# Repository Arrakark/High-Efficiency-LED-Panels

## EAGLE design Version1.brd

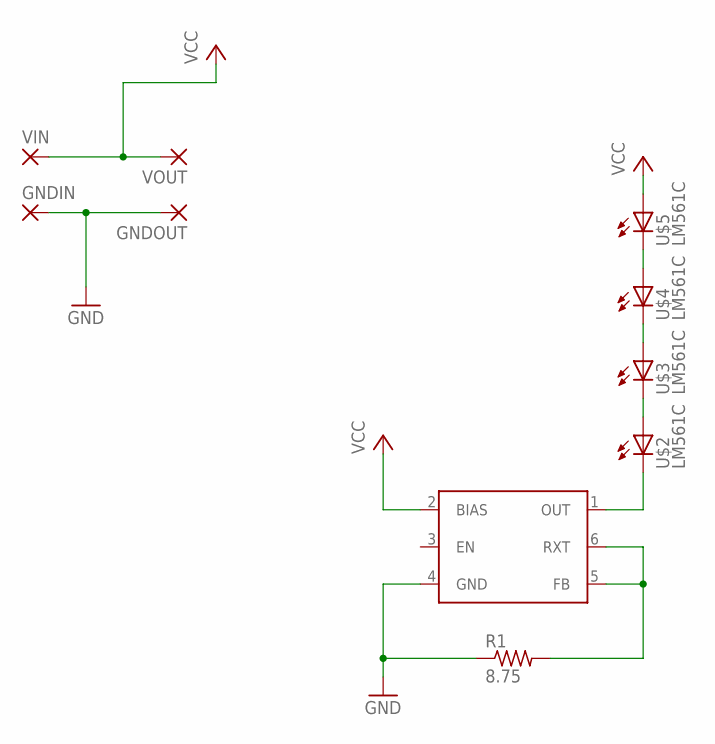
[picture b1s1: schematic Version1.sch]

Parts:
GNDIN: SMD5; SMD2,54-5,08
GNDOUT: SMD5; SMD2,54-5,08
R1: 8.75; R0805
U$1: AL5802; SOT26
U$2, U$3, U$4, U$5: LM561C; LM561CPAD
VIN: SMD5; SMD2,54-5,08
VOUT: SMD5; SMD2,54-5,08

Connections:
GND: GNDIN.1, GNDOUT.1, R1.1, U$1.4 (GND)
unnamed: R1.2, U$1.5 (FB), U$1.6 (RXT)
unnamed: U$4.ANODE (A), U$5.CATH (C)
unnamed: U$3.ANODE (A), U$4.CATH (C)
unnamed: U$2.ANODE (A), U$3.CATH (C)
unnamed: U$1.1 (OUT), U$2.CATH (C)
VCC: U$1.2 (BIAS), U$5.ANODE (A), VIN.1, VOUT.1

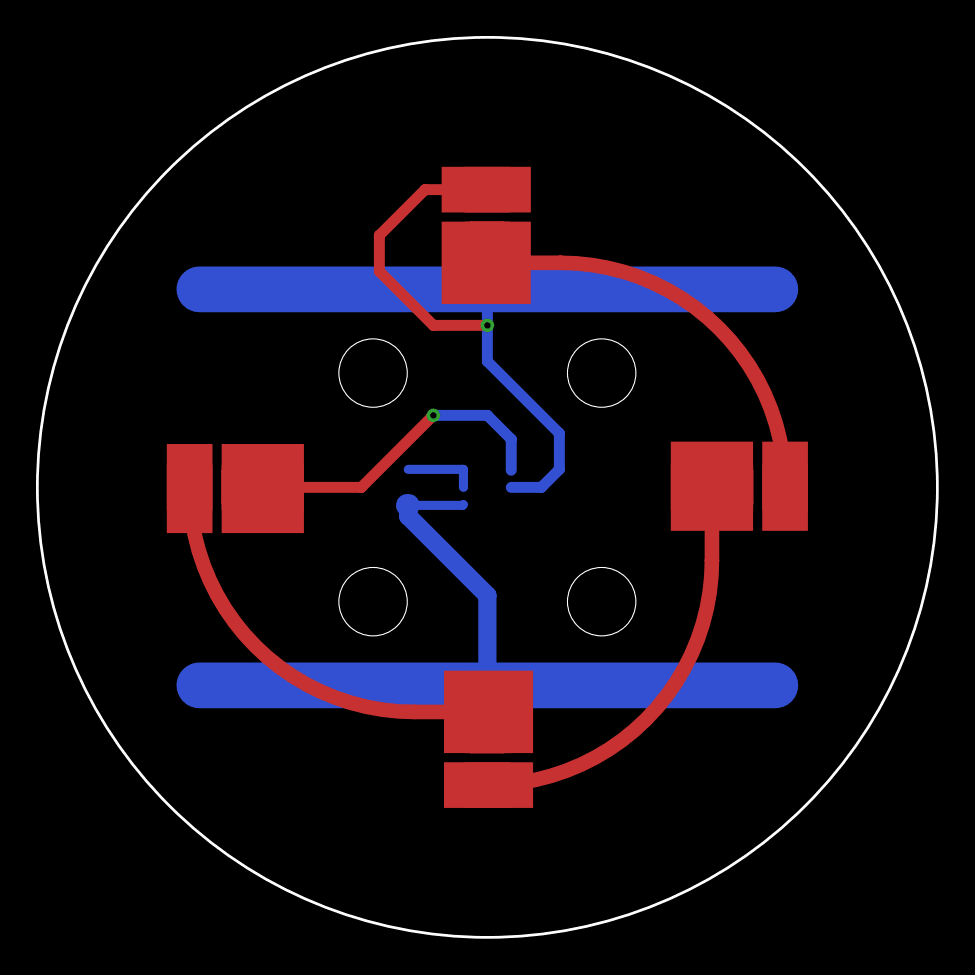
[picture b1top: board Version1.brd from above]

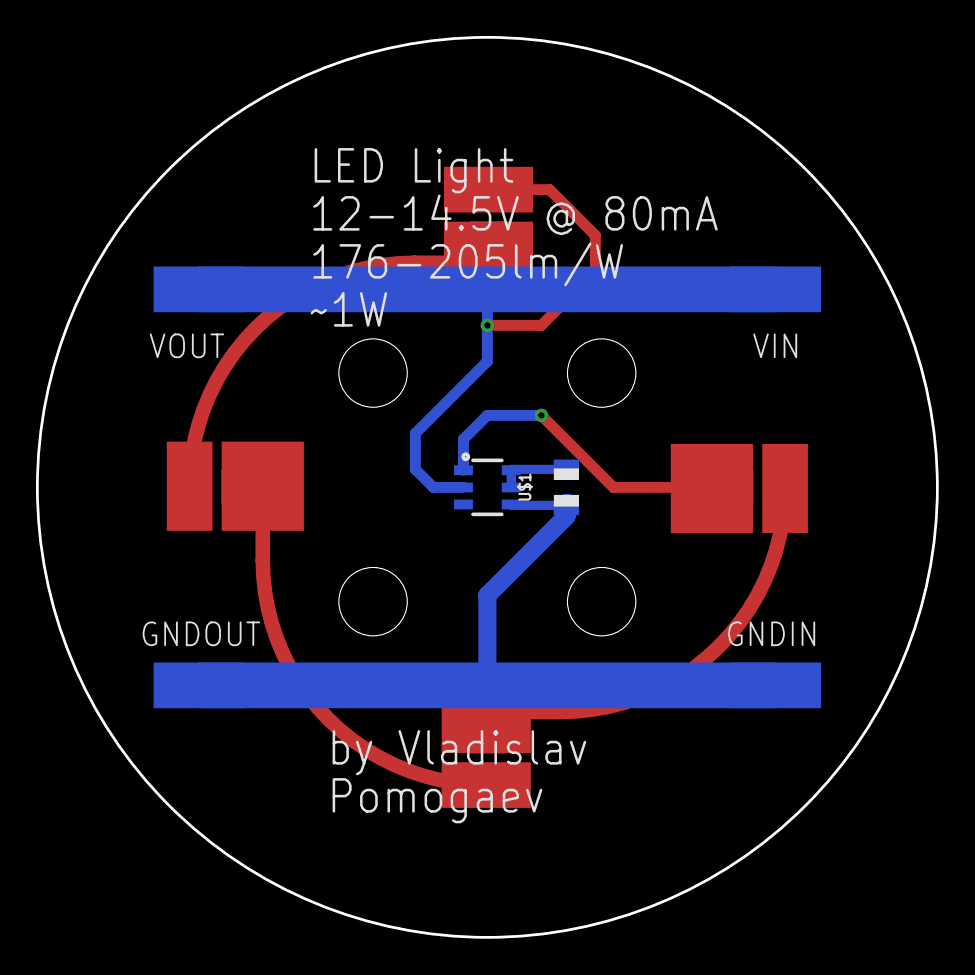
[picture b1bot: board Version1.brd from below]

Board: 2 copper layers, 50.0 x 50.0 mm, 10 parts (6 on the bottom side), 7 nets.

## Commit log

2017-10-08 Added Perfboard Circuit Test
